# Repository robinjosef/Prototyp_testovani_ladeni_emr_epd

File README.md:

"# Prototyp_testovani_ladeni_emr_epd"

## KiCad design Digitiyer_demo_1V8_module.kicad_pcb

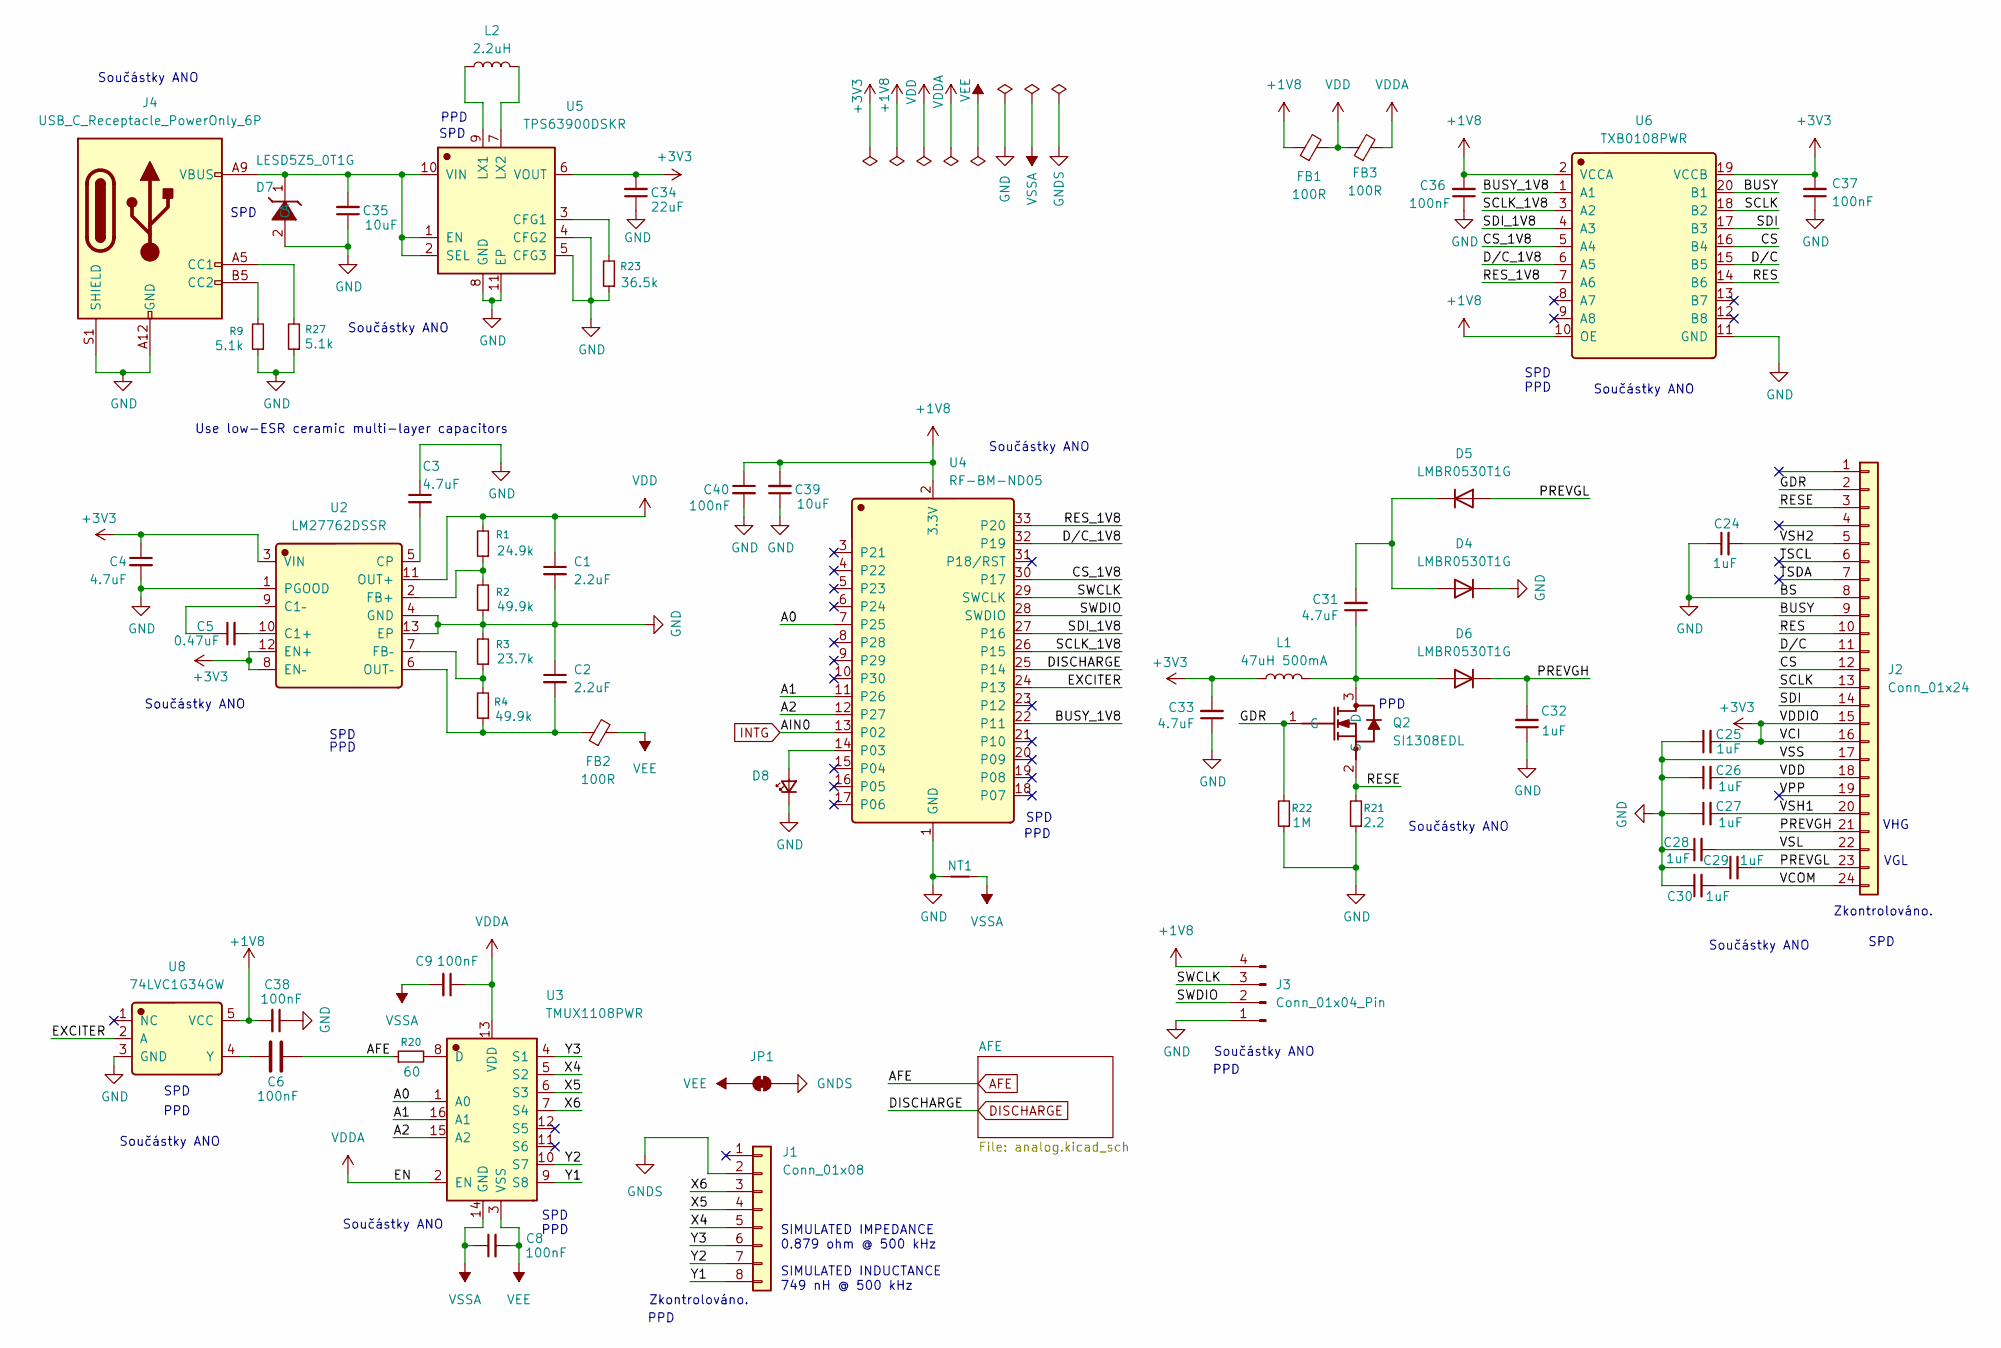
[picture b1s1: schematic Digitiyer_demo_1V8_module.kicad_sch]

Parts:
C1, C2: 2.2uF; C_0402_1005Metric
C3, C4: 4.7uF; C_0402_1005Metric
C5: 0.47uF; C_0603_1608Metric
C6: 100nF; C_0603_1608Metric_Pad1.08x0.95mm_HandSolder
C8, C9, C38, C40: 100nF; C_0603_1608Metric
C24, C25, C26, C27, C28, C29, C30, C32: 1uF; C_0603_1608Metric
C31, C33: 4.7uF; C_0805_2012Metric
C34: 22uF; C_0603_1608Metric
C35, C39: 10uF; C_0402_1005Metric
C36, C37: 100nF; C_0402_1005Metric
D4, D5, D6: LMBR0530T1G; D_SOD-123
D7: LESD5Z5_0T1G; D_SOD-523; Manufacturer Part LESD5Z5.0T1G; LCSC C136171
D8: LED_Small; LED_0603_1608Metric
FB1, FB2, FB3: 100R; L_0805_2012Metric
J1: Conn_01x08; FPC-05F-8PH20
J2: Conn_01x24; FPC-0_5FX-24PWBH15
J3: Conn_01x04_Pin; PinHeader_1x04_P2.54mm_Vertical
J4: USB_C_Receptacle_PowerOnly_6P; USB_C_Receptacle_HRO_TYPE-C-31-M-17
JP1: SolderJumper_2_Bridged; SolderJumper-2_P1.3mm_Bridged2Bar_Pad1.0x1.5mm
L1: 47uH 500mA; L_Wuerth_MAPI-3015
L2: 2.2uH; L_1008_2520Metric
NT1: NetTie_2; NetTie-2_SMD_Pad0.5mm
Q2: SI1308EDL; SOT-323_SC-70_Handsoldering; Manufacturer Part SI1308EDL-VB; LCSC C4355112
R1: 24.9k; R_0603_1608Metric
R2, R4: 49.9k; R_0603_1608Metric
R3: 23.7k; R_0603_1608Metric
R9, R27: 5.1k; R_0402_1005Metric
R20: 60; R_0603_1608Metric
R21: 2.2; R_0603_1608Metric
R22: 1M; R_0603_1608Metric
R23: 36.5k; R_0603_1608Metric_Pad0.98x0.95mm_HandSolder
U2: LM27762DSSR; WSON-12-1EP_3x2mm_P0.5mm_EP1x2.65; Manufacturer Part LM27762DSSR; LCSC C473398
U3: TMUX1108PWR; TSSOP-16_4.4x5mm_P0.65mm; Manufacturer Part TMUX1108PWR; LCSC C1021800
U4: RF-BM-ND05; Manufacturer Part RF-BM-ND05; LCSC C5187534
U5: TPS63900DSKR; Manufacturer Part TPS63900DSKR; LCSC C1518762
U6: TXB0108PWR; TSSOP-20_4.4x6.5mm_P0.65mm; Manufacturer Part TXB0108PWR; LCSC C53406
U8: 74LVC1G34GW; SOT-353_SC-70-5; Manufacturer Part 74LVC1G34GW; LCSC C52140426

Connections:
+1V8: C36.2, C38.2, C39.2, C40.1, FB1.1, J3.4, U4.2 (3.3V), U6.2 (VCCA), U6.10 (OE), U8.5 (VCC)
+3V3: C4.1, C25.2, C33.2, C34.2, C37.2, J2.15, J2.16, L1.1, U2.3 (VIN), U2.8 (EN–), U2.12 (EN+), U5.6 (VOUT), U6.19 (VCCB)
/A0: U3.1 (A0), U4.7 (P25)
/A1: U3.16 (A1), U4.11 (P26)
/A2: U3.15 (A2), U4.12 (P27)
/BUSY: J2.9, U6.20 (B1)
/BUSY_1V8: U4.22 (P11), U6.1 (A1)
/CS: J2.12, U6.16 (B4)
/CS_1V8: U4.30 (P17), U6.5 (A4)
/D/C: J2.11, U6.15 (B5)
/D/C_1V8: U4.32 (P19), U6.6 (A5)
/EXCITER: U4.24 (P13), U8.2 (A)
/GDR: J2.2, Q2.1 (G), R22.2
/PREVGH: C32.2, D6.1 (K), J2.21
/PREVGL: C29.2, D5.2 (A), J2.23
/RES: J2.10, U6.14 (B6)
/RESE: J2.3, Q2.2 (S), R21.2
/RES_1V8: U4.33 (P20), U6.7 (A6)
/SCLK: J2.13, U6.18 (B2)
/SCLK_1V8: U4.26 (P15), U6.3 (A2)
/SDI: J2.14, U6.17 (B3)
/SDI_1V8: U4.27 (P16), U6.4 (A3)
/SWCLK: J3.3, U4.29 (SWCLK)
/SWDIO: J3.2, U4.28 (SWDIO)
/TSCL: J2.6
/TSDA: J2.7
/VCOM: C30.2, J2.24
/VPP: J2.19
/VSH1: C27.2, J2.20
/VSH2: C24.2, J2.5
/VSL: C28.2, J2.22
/X4: J1.5, U3.5 (S2)
/X5: J1.4, U3.6 (S3)
/X6: J1.3, U3.7 (S4)
/Y1: J1.8, U3.9 (S8)
/Y2: J1.7, U3.10 (S7)
/Y3: J1.6, U3.4 (S1)
AFE: C6.2, R20.1; also elsewhere on the board
DISCHARGE: U4.25 (P14); also elsewhere on the board
GND: C1.2, C2.1, C3.1, C4.2, C24.1, C25.1, C26.1, C27.1, C28.1, C29.1, C30.1, C32.1, C33.1, C34.1, C35.1, C36.1, C37.1, C38.1, C39.1, C40.2, D4.1 (K), D7.2 (A), D8.1 (K), J2.8, J2.17, J3.1, J4.A12 (GND), J4.B12 (GND), J4.S1 (SHIELD), NT1.1, R2.1, R3.2, R9.1, R21.1, R22.1, R23.1, R27.1, U2.1 (PGOOD), U2.4 (GND), U2.13 (EP), U4.1 (GND), U5.4 (CFG2), U5.5 (CFG3), U5.8 (GND), U5.11 (EP), U6.11 (GND), U8.3 (GND)
GNDS: J1.2, JP1.2 (B)
INTG: U4.13 (P02); also elsewhere on the board
unnamed: C31.2, D4.2 (A), D5.1 (K)
unnamed: C31.1, D6.2 (A), L1.2, Q2.3 (D)
unnamed: C35.2, D7.1 (C), J4.A9 (VBUS), J4.B9 (VBUS), U5.1 (EN), U5.2 (SEL), U5.10 (VIN)
unnamed: D8.2 (A), U4.14 (P03)
unnamed: J4.A5 (CC1), R27.2
unnamed: J4.B5 (CC2), R9.2
unnamed: C5.2, U2.10 (C1+)
unnamed: C5.1, U2.9 (C1–)
unnamed: C3.2, U2.5 (CP)
unnamed: R1.1, R2.2, U2.2 (FB+)
unnamed: R3.1, R4.2, U2.7 (FB–)
unnamed: C2.2, FB2.1, R4.1, U2.6 (OUT–)
unnamed: R20.2, U3.8 (D)
unnamed: R23.2, U5.3 (CFG1)
unnamed: L2.1, U5.9 (LX1)
unnamed: L2.2, U5.7 (LX2)
unnamed: C6.1, U8.4 (Y)
VDD: C1.1, C26.2, FB1.2, FB3.1, J2.18, R1.2, U2.11 (OUT+)
VDDA: C9.1, FB3.2, U3.2 (EN), U3.13 (VDD); also elsewhere on the board
VEE: C8.2, FB2.2, JP1.1 (A), U3.3 (VSS); also elsewhere on the board
VSSA: C8.1, C9.2, NT1.2, U3.14 (GND); also elsewhere on the board

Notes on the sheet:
PPD
Součástky ANO
SPD
VGL
Use low-ESR ceramic multi-layer capacitors
SIMULATED INDUCTANCE 749 nH @ 500 kHz
Zkontrolováno.
VHG
SIMULATED IMPEDANCE 0.879 ohm @ 500 kHz

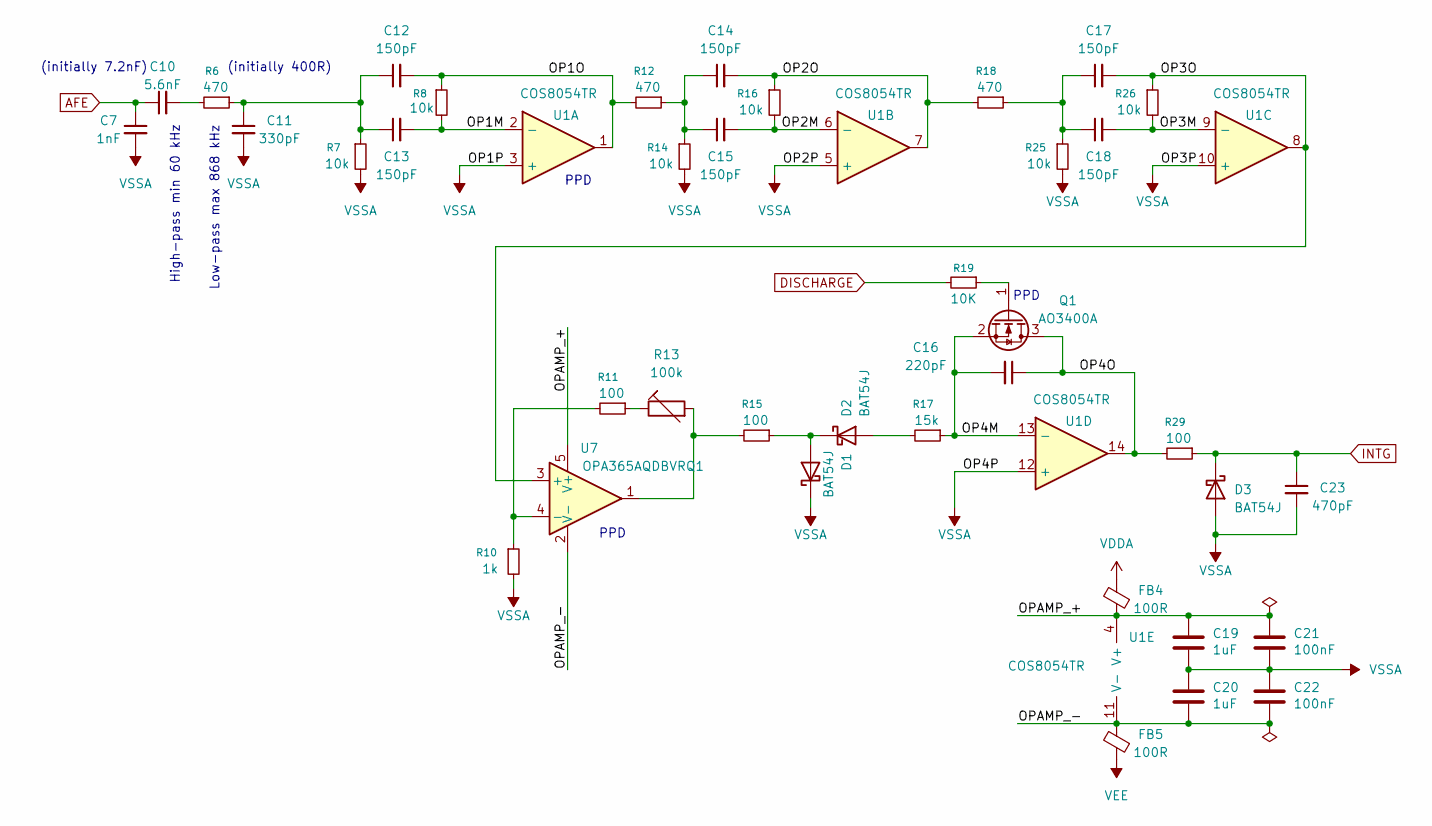
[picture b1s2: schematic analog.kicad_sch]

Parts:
C7: 1nF; C_0402_1005Metric
C10: 5.6nF; C_0603_1608Metric_Pad1.08x0.95mm_HandSolder
C11: 330pF; C_0603_1608Metric
C12, C13, C14, C15, C17, C18: 150pF; C_0603_1608Metric
C16: 220pF; C_0402_1005Metric
C19, C20: 1uF; C_0603_1608Metric
C21, C22: 100nF; C_0603_1608Metric
C23: 470pF; C_0603_1608Metric
D1, D2, D3: BAT54J; D_SOD-323F
FB4, FB5: 100R; L_0805_2012Metric
Q1: AO3400A; SOT-23
R6, R12, R18: 470; R_0402_1005Metric
R7, R8, R14, R16, R25, R26: 10k; R_0805_2012Metric
R10: 1k; R_0402_1005Metric
R11, R15, R29: 100; R_0402_1005Metric
R13: 100k; Potentiometer_Bourns_3314J_Vertical
R17: 15k; R_0402_1005Metric
R19: 10K; R_0805_2012Metric
U1: COS8054TR; TSSOP-14_4.4x5mm_P0.65mm
U7: OPA365AQDBVRQ1; SOT-23-5_HandSoldering

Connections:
/AFE/OP1M: C13.2, R8.2, U1.2 (-)
/AFE/OP1O: C12.2, R8.1, R12.2, U1.1
/AFE/OP2M: C15.2, R16.2, U1.6 (-)
/AFE/OP2O: C14.2, R16.1, R18.2, U1.7
/AFE/OP3M: C18.2, R26.2, U1.9 (-)
/AFE/OP3O: C17.2, R26.1, U1.8, U7.3 (+)
/AFE/OP4M: C16.2, Q1.2 (S), R17.1, U1.13 (-)
/AFE/OP4O: C16.1, Q1.3 (D), R29.2, U1.14
/AFE/OPAMP_+: C19.1, C21.1, FB4.1, U1.4 (V+), U7.5 (V+)
/AFE/OPAMP_-: C20.2, C22.2, FB5.2, U1.11 (V-), U7.2 (V-)
AFE: C7.1, C10.1; also elsewhere on the board
DISCHARGE: R19.2; also elsewhere on the board
INTG: C23.1, D3.1 (K), R29.1; also elsewhere on the board
unnamed: C10.2, R6.2
unnamed: C11.1, C12.1, C13.1, R6.1, R7.1
unnamed: C14.1, C15.1, R12.1, R14.1
unnamed: C17.1, C18.1, R18.1, R25.1
unnamed: D1.2 (A), D2.1 (K), R15.1
unnamed: D2.2 (A), R17.2
unnamed: Q1.1 (G), R19.1
unnamed: R11.1, R13.1
unnamed: R13.2, R15.2, U7.1
unnamed: R10.1, R11.2, U7.4 (-)
VDDA: FB4.2; also elsewhere on the board
VEE: FB5.1; also elsewhere on the board
VSSA: C7.2, C11.2, C19.2, C20.1, C21.2, C22.1, C23.2, D1.1 (K), D3.2 (A), R7.2, R10.2, R14.2, R25.2, U1.3 (+), U1.5 (+), U1.10 (+), U1.12 (+); also elsewhere on the board

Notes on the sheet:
PPD
High-pass min 60 kHz
Low-pass max 868 kHz
(initially 400R)
(initially 7.2nF)

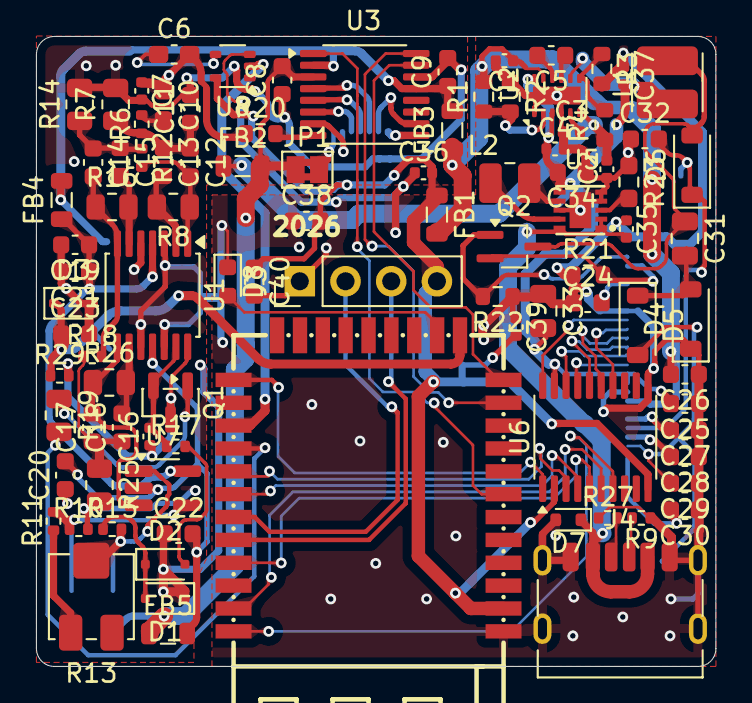
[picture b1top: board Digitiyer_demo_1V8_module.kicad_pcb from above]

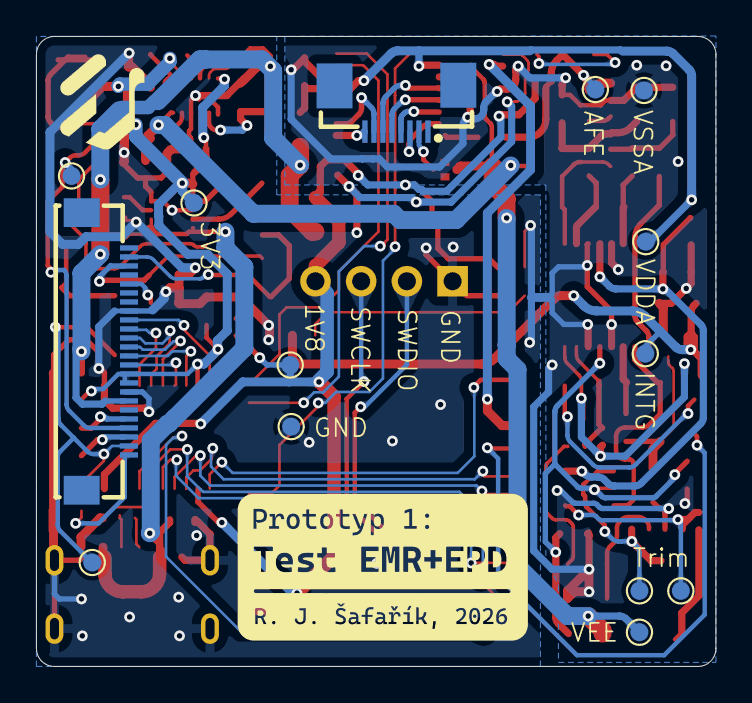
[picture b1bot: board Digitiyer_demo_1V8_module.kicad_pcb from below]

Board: 2 copper layers, 37.8 x 35.0 mm, 97 parts (3 on the bottom side), 80 nets.
